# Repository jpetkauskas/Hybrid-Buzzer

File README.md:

# Hybrid Quiz Bowl Buzzers
***[Try a demo of the Reader Console here!](https://jpetkauskas.github.io/Hybrid-Buzzer/)***

This project uses three ESP32 based boards communicating via a unidirectional ESP-NOW link for robust, low latency Quizbowl lockout arbitration. A custom autopairing algorithm eliminates hardcoded MAC addresses and improves usability. The receiver also runs a novel SoftAP web server which hosts a scoring terminal for the reader, digitizing and simplifying tedious quizbowl scoring and adding analysis capability. Synchronized buzzer timing system  coordinates transmitter nodes based on receiver time, arbitrating winner based on incoming timestamps so that near-simultaneous buzzes aren't dropped, reaching 50/50 performance on true-simultaneous buzzes, 95/5 on 25uS deltas, and 100/0 correct arbitration for deltas >=50 uS (0.5 ms).

I built these buzzers to replace my high school teams' aging wired set. The hybrid approach—wireless team stations with wired individual clickers—is more convenient than fully wired systems and scales more efficiently than fully wireless approaches. 

[See my writeup for more details.](https://justinaspetkauskas.com/writeups/hybrid-buzzers)

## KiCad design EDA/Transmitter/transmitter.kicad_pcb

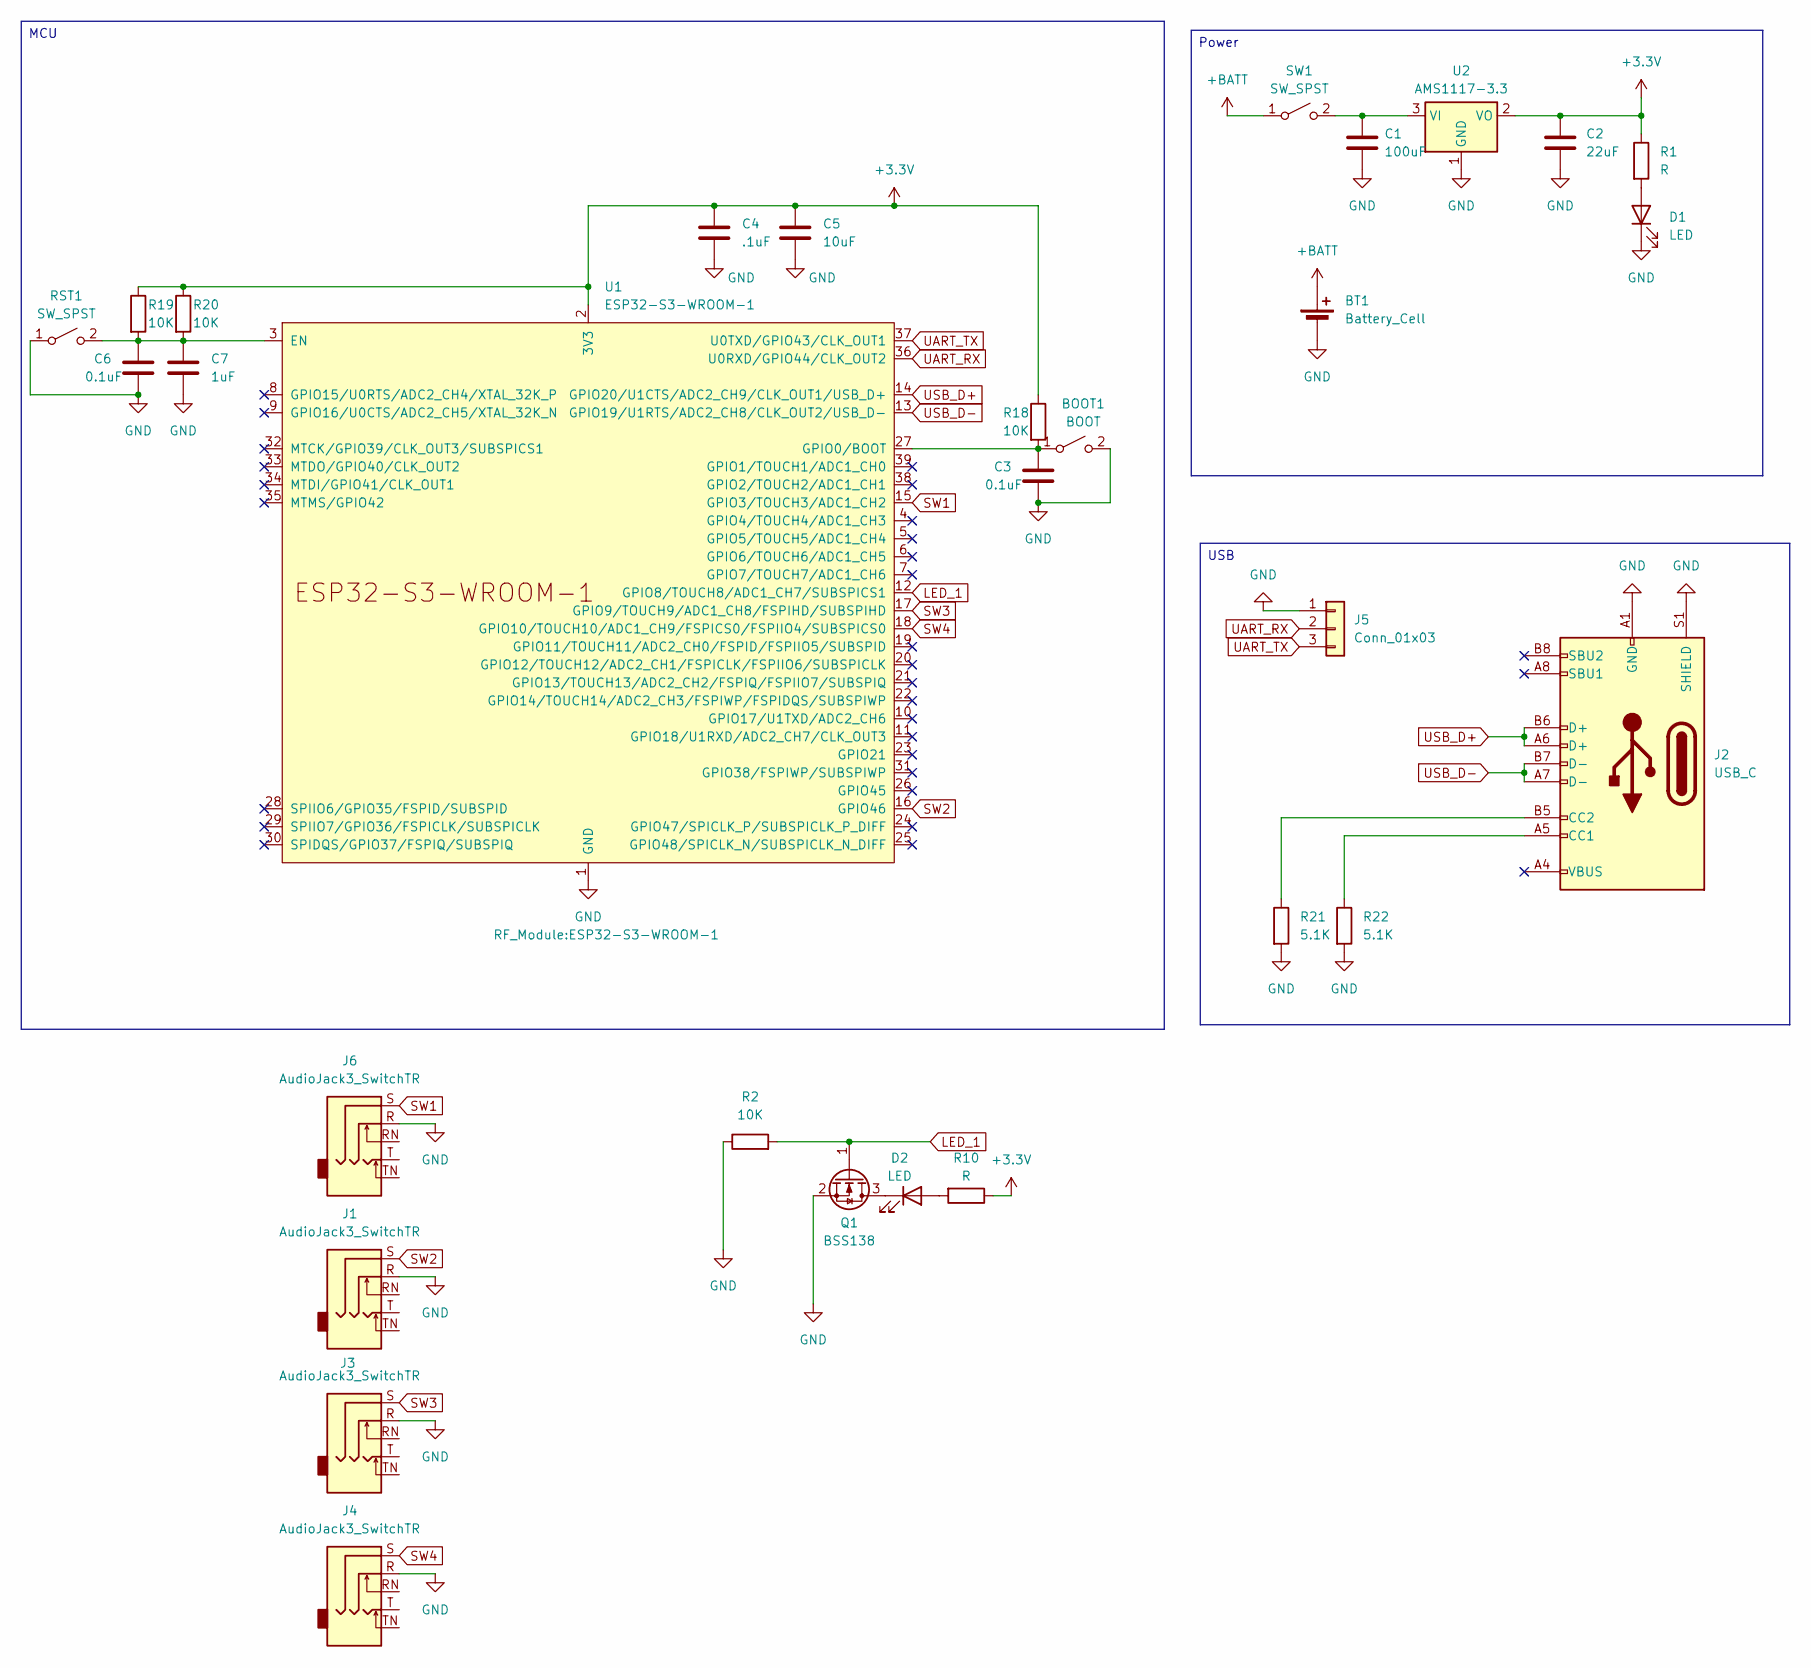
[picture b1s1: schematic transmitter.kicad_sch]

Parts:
BOOT1: BOOT; SW_SPST_B3U-1000P
BT1: Battery_Cell; PinHeader_1x02_P2.54mm_Vertical
C1: 100uF; C_0603_1608Metric
C2: 22uF; C_0603_1608Metric
C3, C6: 0.1uF; C_0603_1608Metric
C4: .1uF; C_0603_1608Metric
C5: 10uF; C_0603_1608Metric
C7: 1uF; C_0603_1608Metric
D1, D2: LED; LED_D3.0mm
J1, J3, J4, J6: AudioJack3_SwitchTR; Jack_3.5mm_CUI_SJ1-3525N_Horizontal
J2: USB_C; USB_C_Receptacle_G-Switch_GT-USB-7010ASV
J5: Conn_01x03; PinHeader_1x03_P2.54mm_Vertical
Q1: BSS138; SOT-23
R1, R10: R; R_0603_1608Metric
R2, R18, R19, R20: 10K; R_0603_1608Metric
R21, R22: 5.1K; R_0603_1608Metric
RST1: SW_SPST; SW_SPST_B3U-1000P
SW1: SW_SPST; SW_Slide_SPDT_Angled_CK_OS102011MA1Q
U1: ESP32-S3-WROOM-1
U2: AMS1117-3.3; SOT-223-3_TabPin2

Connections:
+3.3V: C2.1, C4.1, C5.1, R1.1, R10.1, R18.1, R19.1, R20.1, U1.2 (3V3), U2.2 (VO)
+BATT: BT1.1 (+), SW1.1 (A)
GND: BOOT1.2 (B), BT1.2 (-), C1.2, C2.2, C3.2, C4.2, C5.2, C6.2, C7.2, D1.1 (K), J1.R, J2.A1 (GND), J2.A12 (GND), J2.B1 (GND), J2.B12 (GND), J2.S1 (SHIELD), J3.R, J4.R, J5.1, J6.R, Q1.2 (S), R2.1, R21.2, R22.2, RST1.1 (A), U1.1 (GND), U1.40 (GND), U1.41 (GND), U2.1 (GND)
LED_1: Q1.1 (G), R2.2, U1.12 (GPIO8/TOUCH8/ADC1_CH7/SUBSPICS1)
unnamed: BOOT1.1 (A), C3.1, R18.2, U1.27 (GPIO0/BOOT)
unnamed: D1.2 (A), R1.2
unnamed: D2.2 (A), R10.2
unnamed: D2.1 (K), Q1.3 (D)
unnamed: J2.A5 (CC1), R22.1
unnamed: J2.B5 (CC2), R21.1
unnamed: C6.1, C7.1, R19.2, R20.2, RST1.2 (B), U1.3 (EN)
unnamed: C1.1, SW1.2 (B), U2.3 (VI)
SW1: J6.S, U1.15 (GPIO3/TOUCH3/ADC1_CH2)
SW2: J1.S, U1.16 (GPIO46)
SW3: J3.S, U1.17 (GPIO9/TOUCH9/ADC1_CH8/FSPIHD/SUBSPIHD)
SW4: J4.S, U1.18 (GPIO10/TOUCH10/ADC1_CH9/FSPICS0/FSPIIO4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)
UART_RX: J5.2, U1.36 (U0RXD/GPIO44/CLK_OUT2)
UART_TX: J5.3, U1.37 (U0TXD/GPIO43/CLK_OUT1)
USB_D+: J2.A6 (D+), J2.B6 (D+), U1.14 (GPIO20/U1CTS/ADC2_CH9/CLK_OUT1/USB_D+)
USB_D-: J2.A7 (D-), J2.B7 (D-), U1.13 (GPIO19/U1RTS/ADC2_CH8/CLK_OUT2/USB_D-)

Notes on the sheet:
USB
MCU
Power

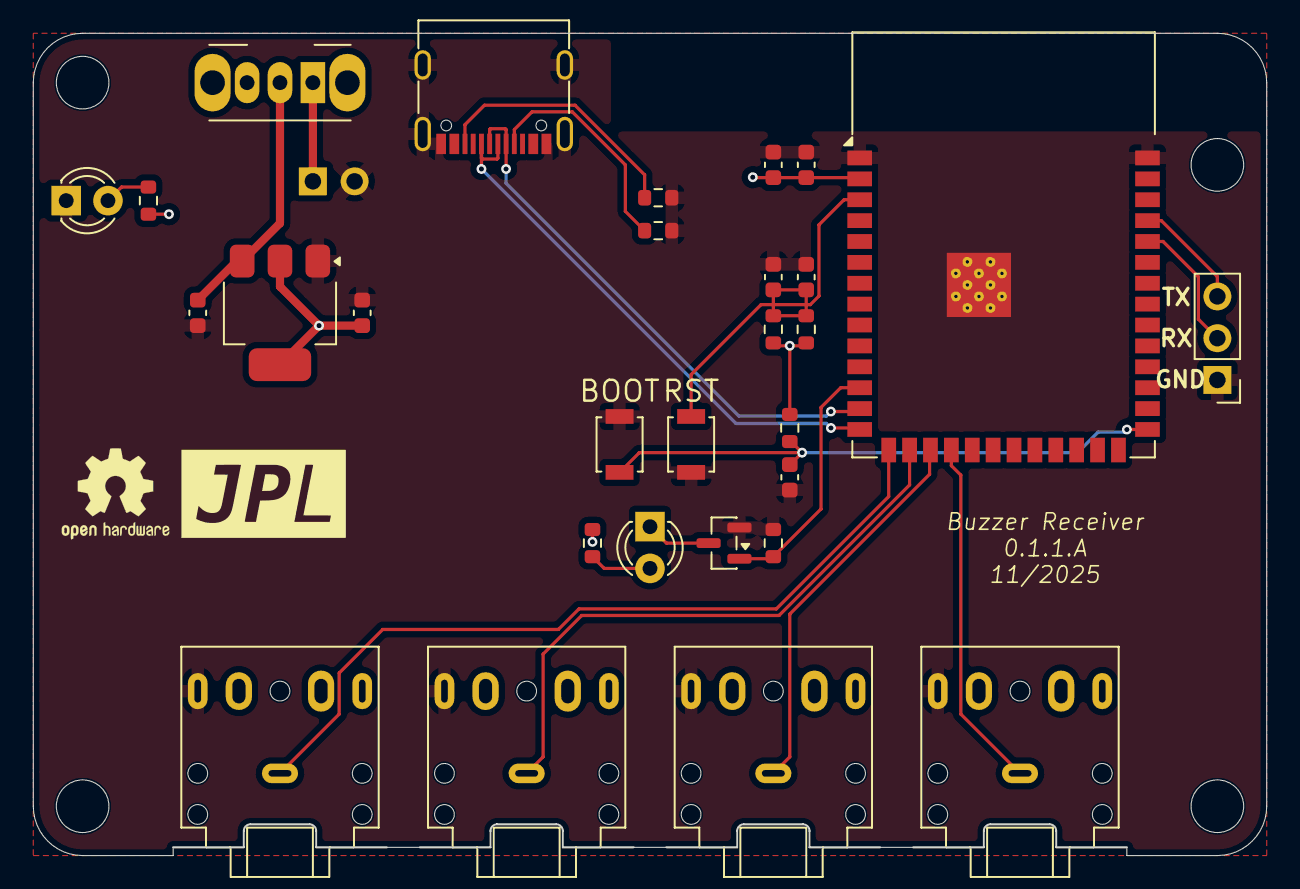
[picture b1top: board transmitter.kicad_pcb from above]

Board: 2 copper layers, 74.9 x 49.9 mm, 30 parts (1 on the bottom side), 20 nets.

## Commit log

2026-05-04 .gitignore
2026-05-04 README
2026-05-04 Flash Test
2026-05-04 roadmap
2026-05-04 Fix formatting of project title in README
2026-05-05 transmitter
2026-05-05 started receiver boilerplate
2026-05-06 fixed pin 3 bug
2026-05-06 breaks in switch
2026-05-07 Receiver!
2026-05-07 buzz refinement
2026-05-07 Add two-way buzzing feature to README
2026-05-07 Updating packet protocol to include transmitting mac to later support peer-to-peer backconfirmation
2026-05-07 prototyping MAC sharing
2026-05-07 scuffed autopairing test
2026-05-12 abstracting button logic to new header
2026-05-16 Abstraction
2026-05-16 receiver abstraction
2026-05-16 refactored receiver buzz scheduling
2026-05-16 gitignore
2026-05-26 unwinding
2026-05-26 wireless.h
2026-05-26 housekeeping
2026-05-28 pictures
2026-05-29 memcpy mac comparison (doesn't work)
2026-05-29 semaphore instead of blocking while loop for handshake
2026-05-29 led initialization before flashing
2026-05-29 transmitter-side wireless pairing protocol
2026-05-29 pairing sequence
2026-05-30 RECEIVER AUTOPAIRING SCAFFOLDING COMPLETE
2026-05-30 autopair+semaphor unblocking, unresolved bug causes crash after buzz
2026-05-31 autopair algorithm complete, memcmp bug unresolved
2026-05-31 fixed memcpy bug
2026-05-31 Transmitter side handshake verification
2026-06-01 automatic team assignment
2026-06-01 buzz abstraction
2026-06-03 finalized autopair
2026-06-04 SoftAP helloworld
2026-06-04 Print arbitration winner to webserver
2026-06-04 status endpoint polling
2026-06-04 Captive DNS
2026-06-04 clear button
2026-06-04 Scorekeeping
2026-06-04 Packet parsing
2026-06-04 merge
2026-06-04 cad+eda
2026-06-05 csv, lockout, packet handling
2026-06-05 Robust bonus handling
2026-06-07 ota updates, quality of life
2026-06-07 final adjustments
2026-06-07 comment out print statements
2026-06-07 readme spelling
2026-06-08 Demo pages deployment
2026-06-08 Refactor GitHub Pages deployment workflow
2026-06-08 gitignore+pages
2026-06-08 github pages for webserver demo
2026-06-08 update gitignore
2026-06-08 Modify GitHub Actions workflow for server demo
2026-06-08 Pages workflow for webserver demo
2026-06-19 lockout testbed
2026-06-19 millis
2026-06-19 printf out of arbitration loop
2026-06-22 clean
2026-06-22 Clean timestamp arbitration
2026-06-22 cleaning up debugging
